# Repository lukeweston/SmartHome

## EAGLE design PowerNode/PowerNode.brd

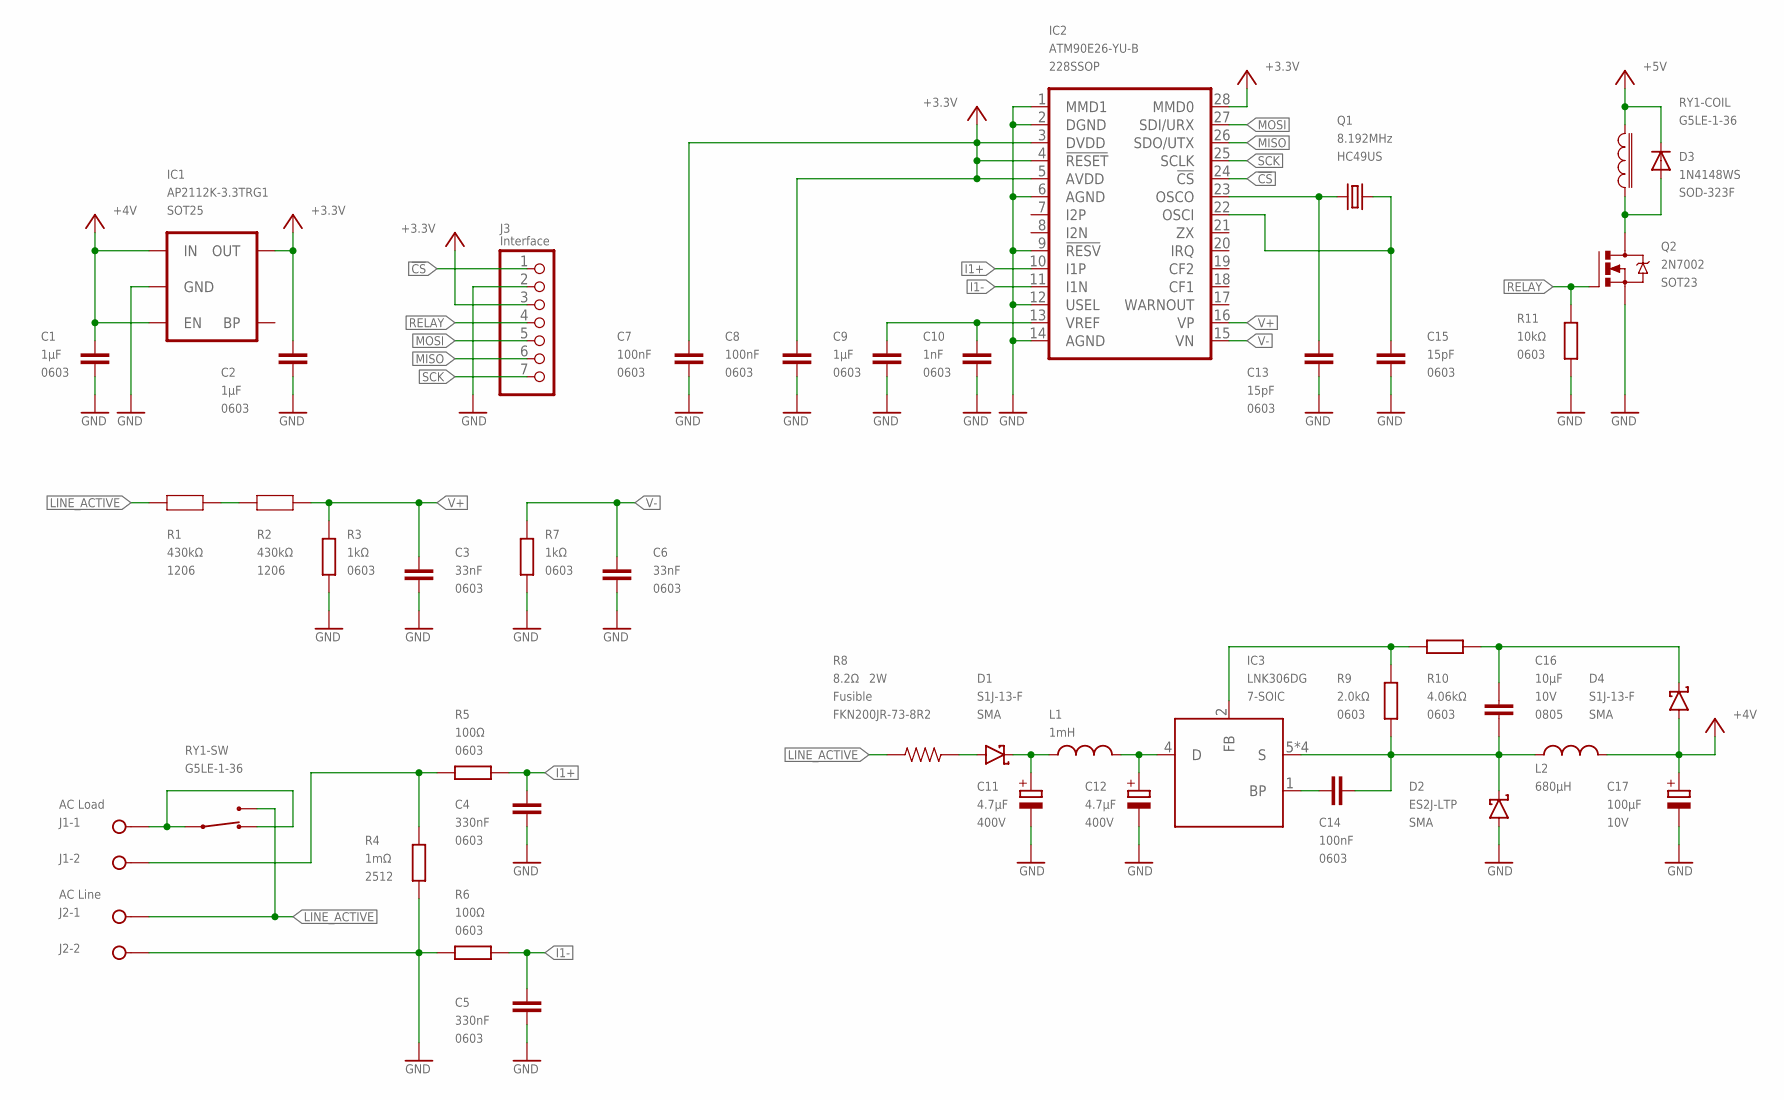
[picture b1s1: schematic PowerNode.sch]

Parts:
C1, C2, C9: 1µF; 0603
C3, C6: 33nF; 0603
C4, C5: 330nF; 0603
C7, C8, C14: 100nF; 0603
C10: 1nF; 0603
C11, C12: 4.7µF; ELECTRO-LARGE; VOLTAGE 400V
C13, C15: 15pF; 0603
C16: 10µF; 0805; VOLTAGE 10V
C17: 100µF; ELECTRO-SMALL; VOLTAGE 10V
D1, D4: S1J-13-F; SMA
D2: ES2J-LTP; SMA
D3: 1N4148WS; SOD-323
IC1: AP2112K-3.3TRG1; SOT23-5
IC2: ATM90E26-YU-B; SSOP-28
IC3: LNK306DG; SO-8C
J1: AC Load; W237-132
J2: AC Line; W237-132
J3: Interface; 1X07
L1: 1mH; RLB0608
L2: 680µH; RLB0914
Q1: 8.192MHz; HC49/S; PARTNO 9B-4.096MBBK-B
Q2: 2N7002; SOT23-3
R1, R2: 430kΩ; 1206; TOLERANCE 1%
R3, R7: 1kΩ; 0603
R4: 1mΩ; R2512; TOLERANCE 1%
R5, R6: 100Ω; 0603
R8: 8.2Ω; FKN200JR-73
R9: 2.0kΩ; 0603
R10: 4.06kΩ; 0603
R11: 10kΩ; 0603
RY1: G5LE-1-36; G5LE

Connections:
!CS: IC2.24 (!CS), J3.1
+3.3V: C2.1, C7.2, C8.2, IC1.5 (OUT), IC2.3 (DVDD), IC2.4 (!RESET), IC2.5 (AVDD), IC2.28 (MMD0), J3.3
+4V: C1.1, C17.+, D3.1 (C), D4.A, IC1.1 (IN), IC1.3 (EN), L2.2, RY1.COIL1 (1)
GND: C1.2, C2.2, C3.1, C4.1, C5.1, C6.1, C7.1, C8.1, C9.2, C10.1, C11.-, C12.-, C13.1, C15.1, C17.-, D2.A, IC1.2 (GND), IC2.1 (MMD1), IC2.2 (DGND), IC2.6 (AGND), IC2.9 (!RESV), IC2.12 (USEL), IC2.14 (AGND), J2.2, J3.2, Q2.2 (S), R3.2, R4.1, R6.2, R7.2, R11.1
I1+: C4.2, IC2.10 (I1P), R5.1
I1-: C5.2, IC2.11 (I1N), R6.1
LINE_ACTIVE: J2.1, R1.1, R8.1, RY1.NO
MISO: IC2.26 (SDO/UTX), J3.6
MOSI: IC2.27 (SDI/URX), J3.5
unnamed: J1.1, RY1.COM, RY1.NC
unnamed: J1.2, R4.2, R5.2
unnamed: D1.A, R8.2
unnamed: C11.+, D1.K, L1.1
unnamed: C12.+, IC3.4 (D), L1.2
unnamed: C14.1, IC3.1 (BP)
unnamed: C14.2, C16.1, D2.K, IC3.5 (S), IC3.6 (S), IC3.7 (S), IC3.8 (S), L2.1, R9.1
unnamed: IC3.2 (FB), R9.2, R10.2
unnamed: C16.2, D4.K, R10.1
unnamed: D3.2 (A), Q2.3 (D), RY1.COIL2 (2)
unnamed: C13.2, IC2.23 (OSCO), Q1.1
unnamed: C15.2, IC2.22 (OSCI), Q1.2
unnamed: R1.2, R2.1
RELAY: J3.4, Q2.1 (G), R11.2
SCK: IC2.25 (SCLK), J3.7
V+: C3.2, IC2.16 (VP), R2.2, R3.1
V-: C6.2, IC2.15 (VN), R7.1
VREF: C9.1, C10.2, IC2.13 (VREF)

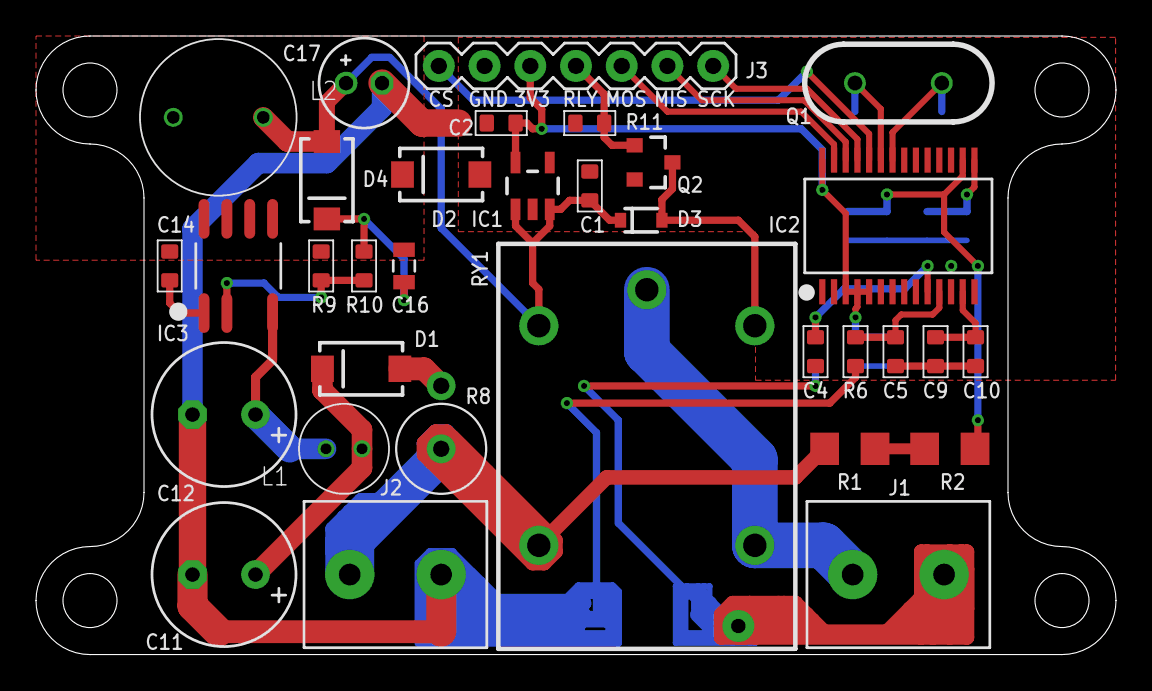
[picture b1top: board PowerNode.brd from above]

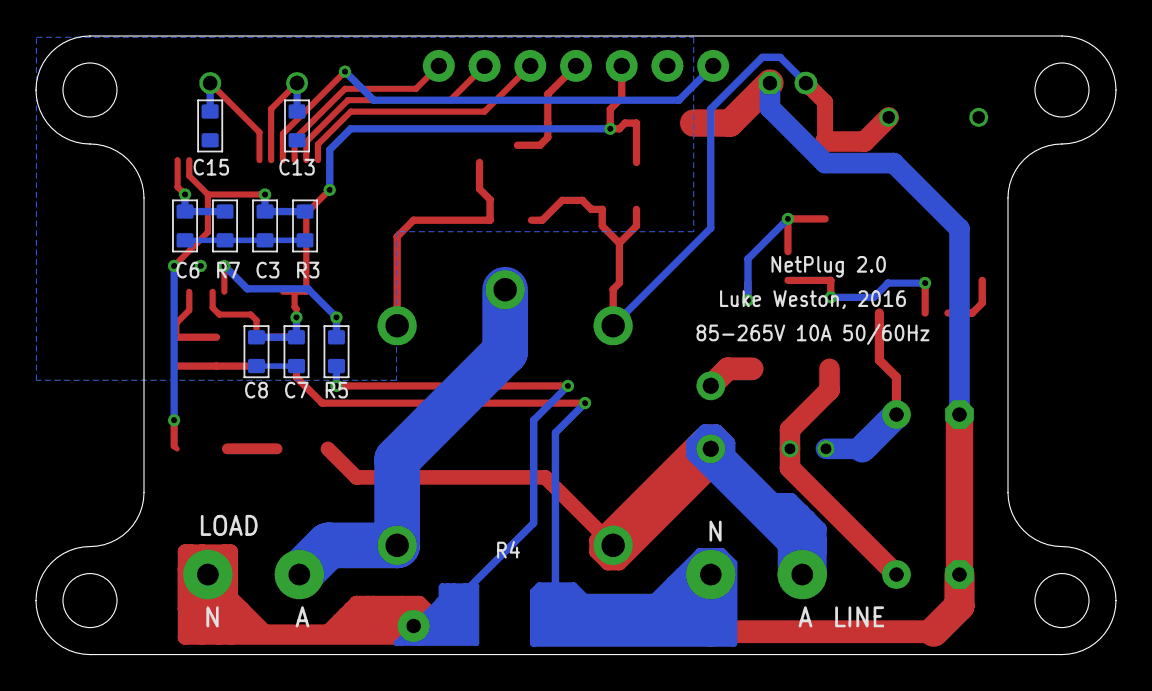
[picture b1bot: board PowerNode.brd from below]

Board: 2 copper layers, 60.0 x 34.4 mm, 43 parts (10 on the bottom side), 27 nets.

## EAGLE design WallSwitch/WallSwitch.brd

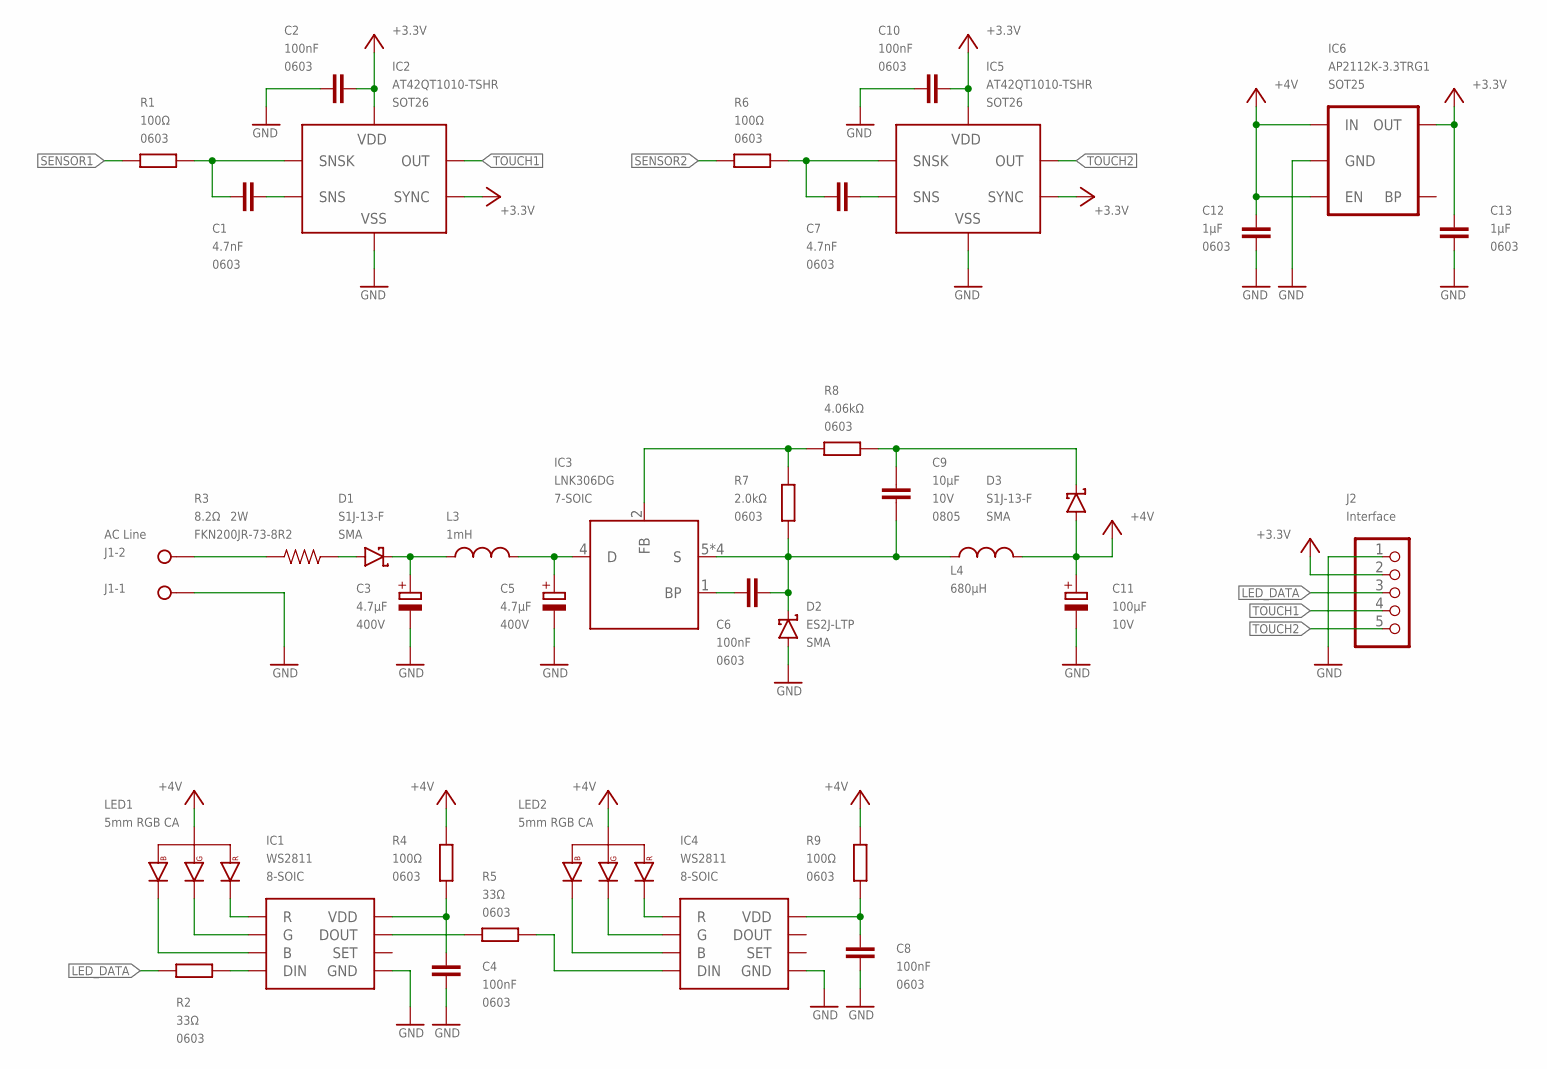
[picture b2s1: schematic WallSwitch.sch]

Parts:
C1, C7: 4.7nF; 0603
C2, C4, C6, C8, C10: 100nF; 0603
C3, C5: 4.7µF; ELECTRO-LARGE; VOLTAGE 400V
C9: 10µF; 0805; VOLTAGE 10V
C11: 100µF; ELECTRO-SMALL; VOLTAGE 10V
C12, C13: 1µF; 0603
D1, D3: S1J-13-F; SMA
D2: ES2J-LTP; SMA
IC1, IC4: WS2811; SOIC-8
IC2, IC5: AT42QT1010-TSHR; SOT23-6
IC3: LNK306DG; SO-8C
IC6: AP2112K-3.3TRG1; SOT23-5
J1: AC Line; W237-132
J2: Interface; 1X05
L3: 1mH; RLB0608
L4: 680µH; RLB0914
LED1, LED2: 5mm RGB CA; LED5MMRGB
R1, R4, R6, R9: 100Ω; 0603
R2, R5: 33Ω; 0603
R3: 8.2Ω; FKN200JR-73
R7: 2.0kΩ; 0603
R8: 4.06kΩ; 0603

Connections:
+3.3V: C2.1, C10.1, C13.1, IC2.5 (VDD), IC2.6 (SYNC), IC5.5 (VDD), IC5.6 (SYNC), IC6.5 (OUT), J2.2
+4V: C11.+, C12.1, D3.A, IC6.1 (IN), IC6.3 (EN), L4.2, LED1.2 (VCC), LED2.2 (VCC), R4.1, R9.1
GND: C2.2, C3.-, C4.2, C5.-, C8.2, C10.2, C11.-, C12.2, C13.2, D2.A, IC1.4 (GND), IC2.2 (VSS), IC4.4 (GND), IC5.2 (VSS), IC6.2 (GND), J1.1, J2.1
LED_DATA: J2.3, R2.2
unnamed: IC1.1 (R), LED1.1 (RED)
unnamed: J1.2, R3.2
unnamed: C7.2, IC5.3 (SNSK), R6.1
unnamed: C7.1, IC5.4 (SNS)
unnamed: C1.2, IC2.3 (SNSK), R1.1
unnamed: C1.1, IC2.4 (SNS)
unnamed: D1.A, R3.1
unnamed: C3.+, D1.K, L3.1
unnamed: C5.+, IC3.4 (D), L3.2
unnamed: C6.2, IC3.1 (BP)
unnamed: C6.1, C9.1, D2.K, IC3.5 (S), IC3.6 (S), IC3.7 (S), IC3.8 (S), L4.1, R7.2
unnamed: IC1.2 (G), LED1.3 (GREEN)
unnamed: IC1.3 (B), LED1.4 (BLUE)
unnamed: IC3.2 (FB), R7.1, R8.1
unnamed: C9.2, D3.K, R8.2
unnamed: IC1.6 (DIN), R2.1
unnamed: C4.1, IC1.8 (VDD), R4.2
unnamed: IC1.5 (DOUT), R5.2
unnamed: IC4.6 (DIN), R5.1
unnamed: IC4.3 (B), LED2.4 (BLUE)
unnamed: IC4.2 (G), LED2.3 (GREEN)
unnamed: IC4.1 (R), LED2.1 (RED)
unnamed: C8.1, IC4.8 (VDD), R9.2
SENSOR1: R1.2
SENSOR2: R6.2
TOUCH1: IC2.1 (OUT), J2.4
TOUCH2: IC5.1 (OUT), J2.5

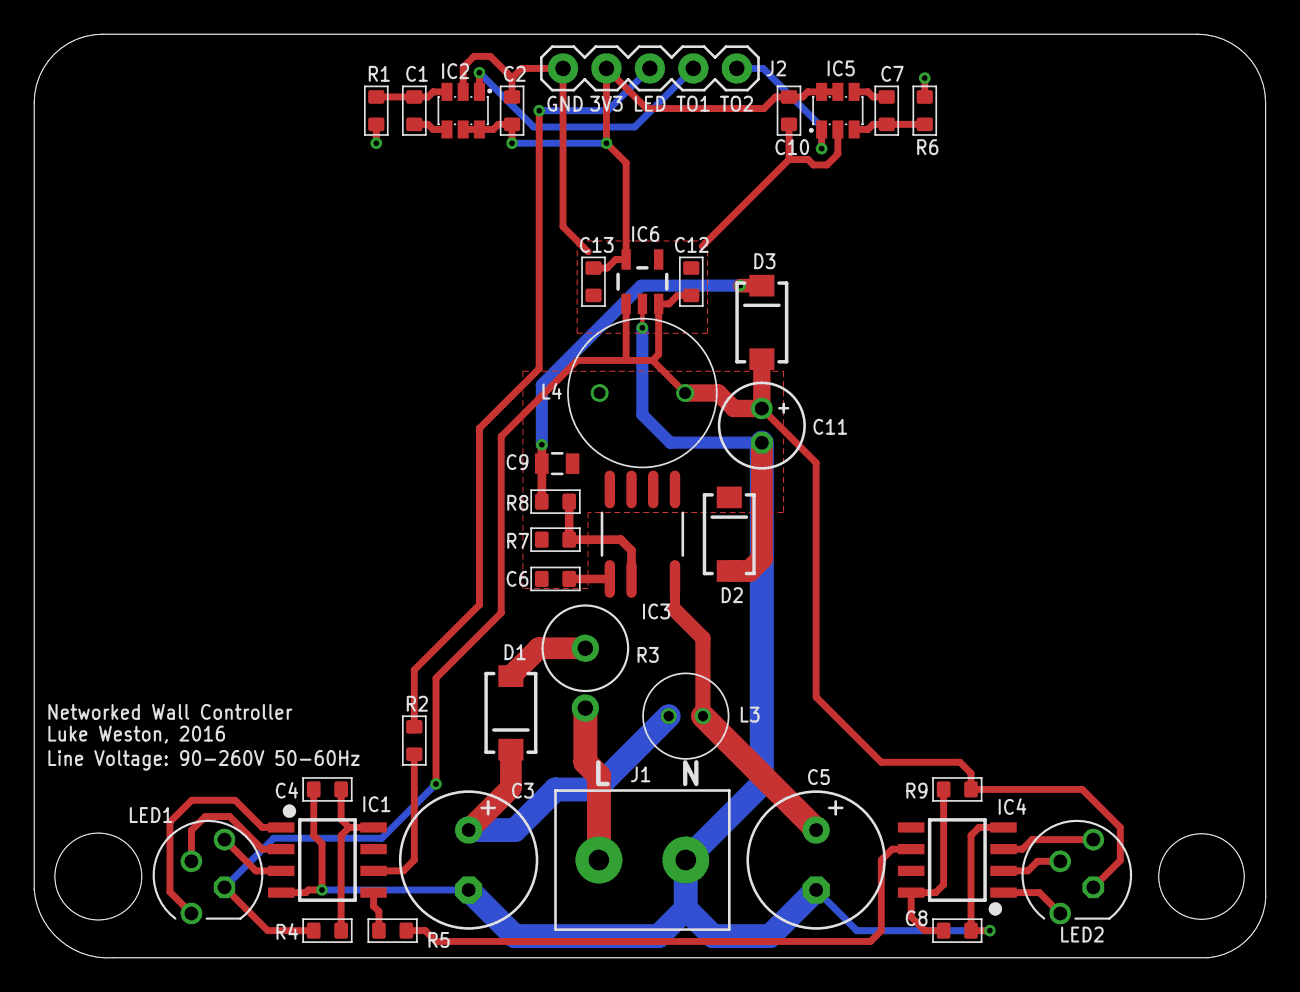
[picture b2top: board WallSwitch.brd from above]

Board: 2 copper layers, 72.0 x 54.0 mm, 37 parts (0 on the bottom side), 29 nets.

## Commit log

2017-04-07 added wall switch files
2017-04-21 added PowerNode files

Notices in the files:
PowerNode/PowerNode.sch:
Open Hardware Licensed under CERN OHL v.1.2 :
Copyright 2017 Luke Weston
